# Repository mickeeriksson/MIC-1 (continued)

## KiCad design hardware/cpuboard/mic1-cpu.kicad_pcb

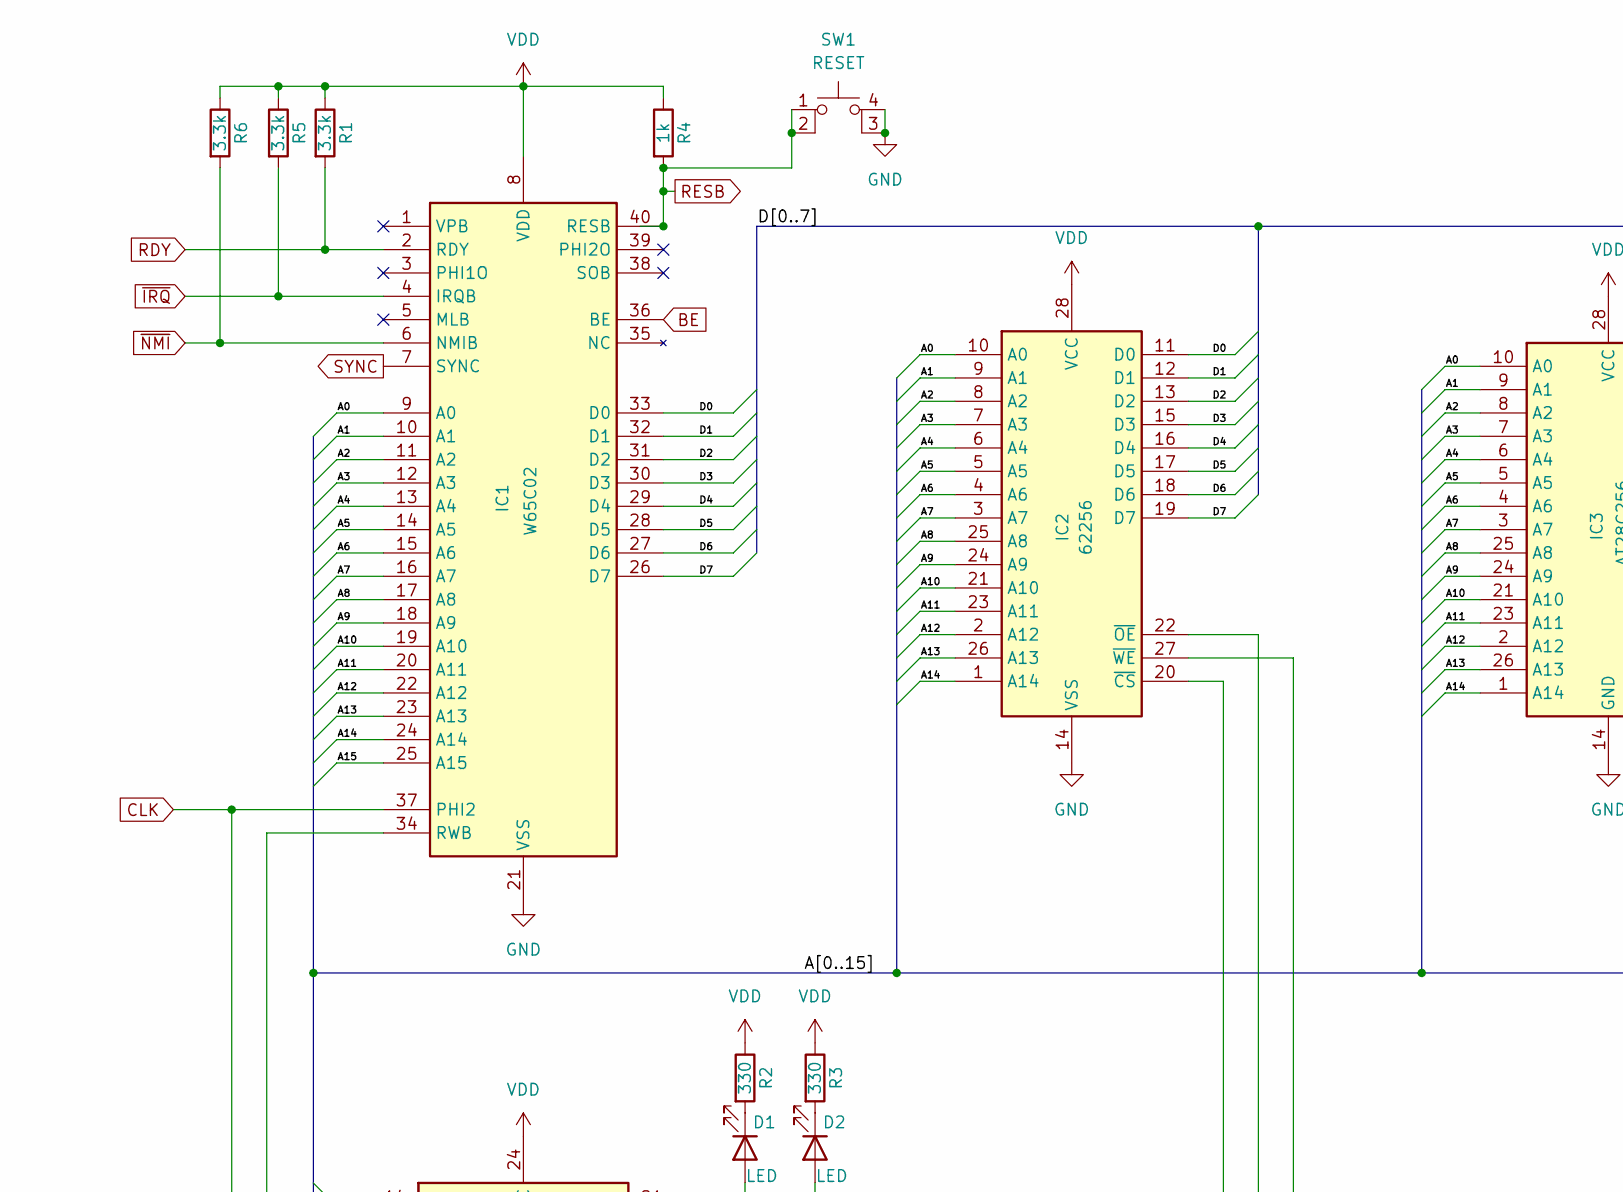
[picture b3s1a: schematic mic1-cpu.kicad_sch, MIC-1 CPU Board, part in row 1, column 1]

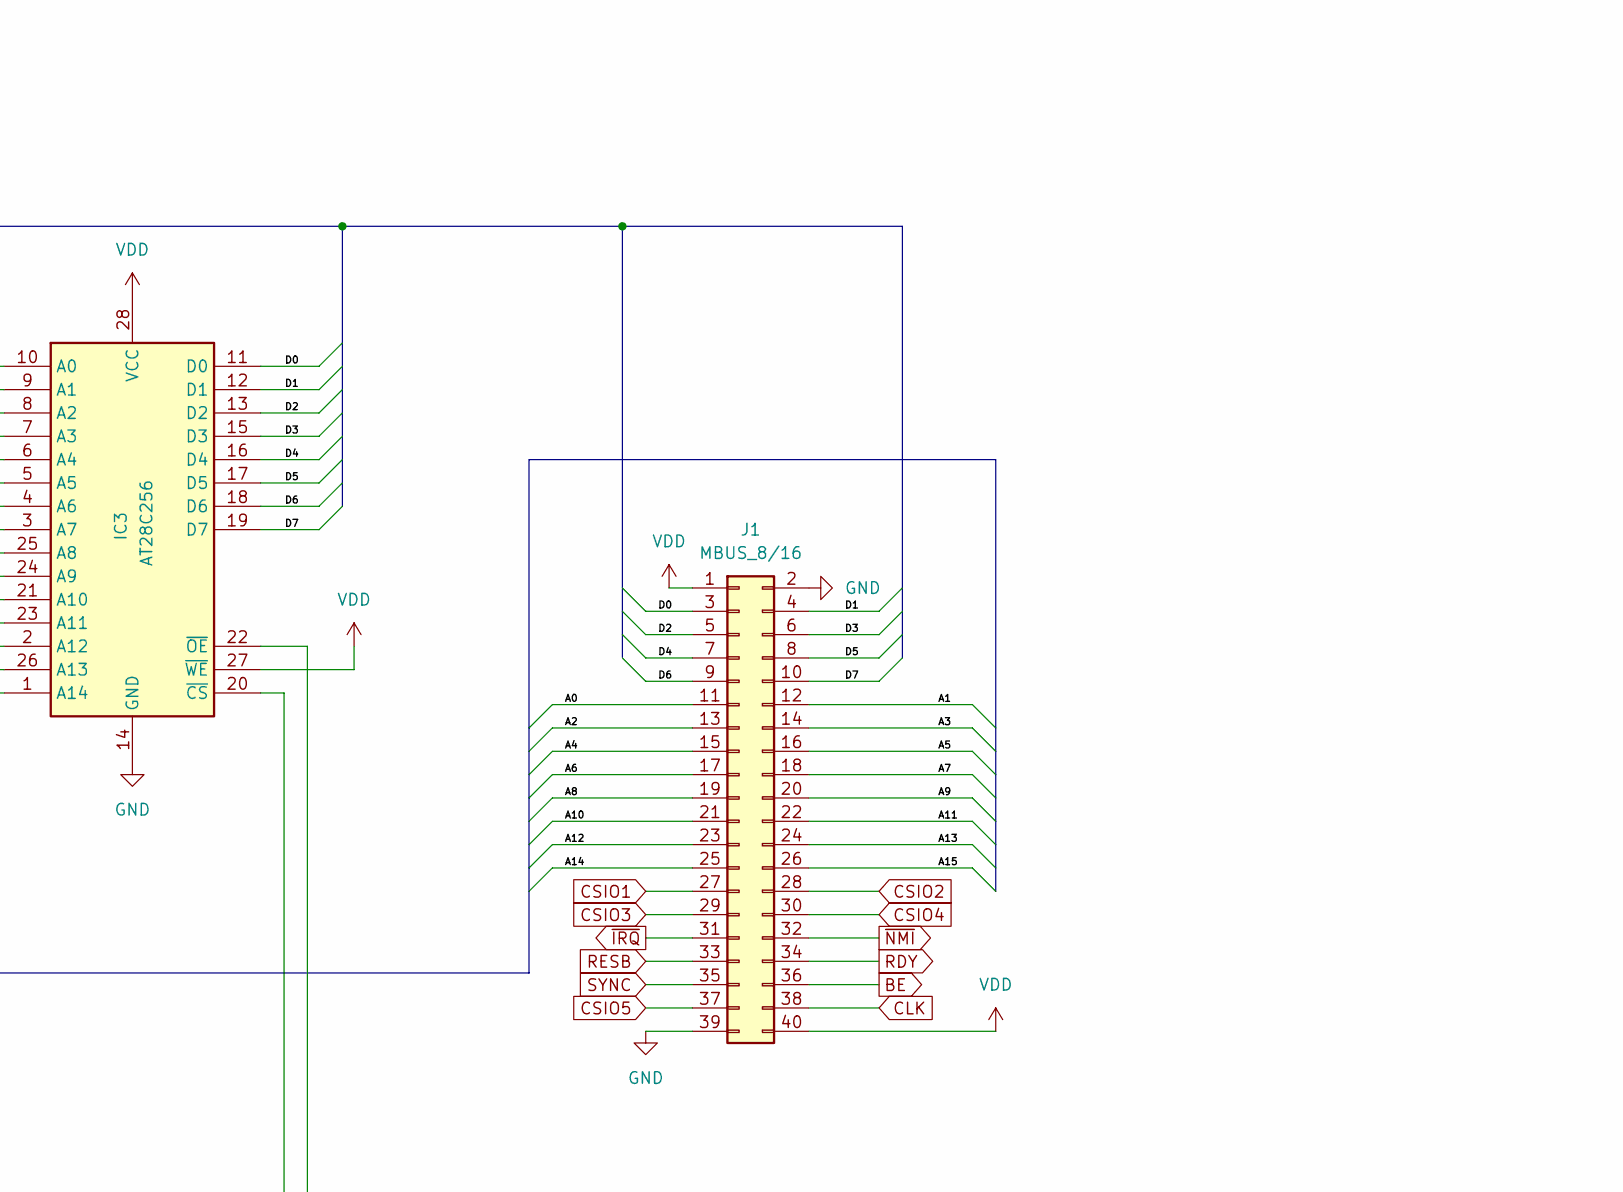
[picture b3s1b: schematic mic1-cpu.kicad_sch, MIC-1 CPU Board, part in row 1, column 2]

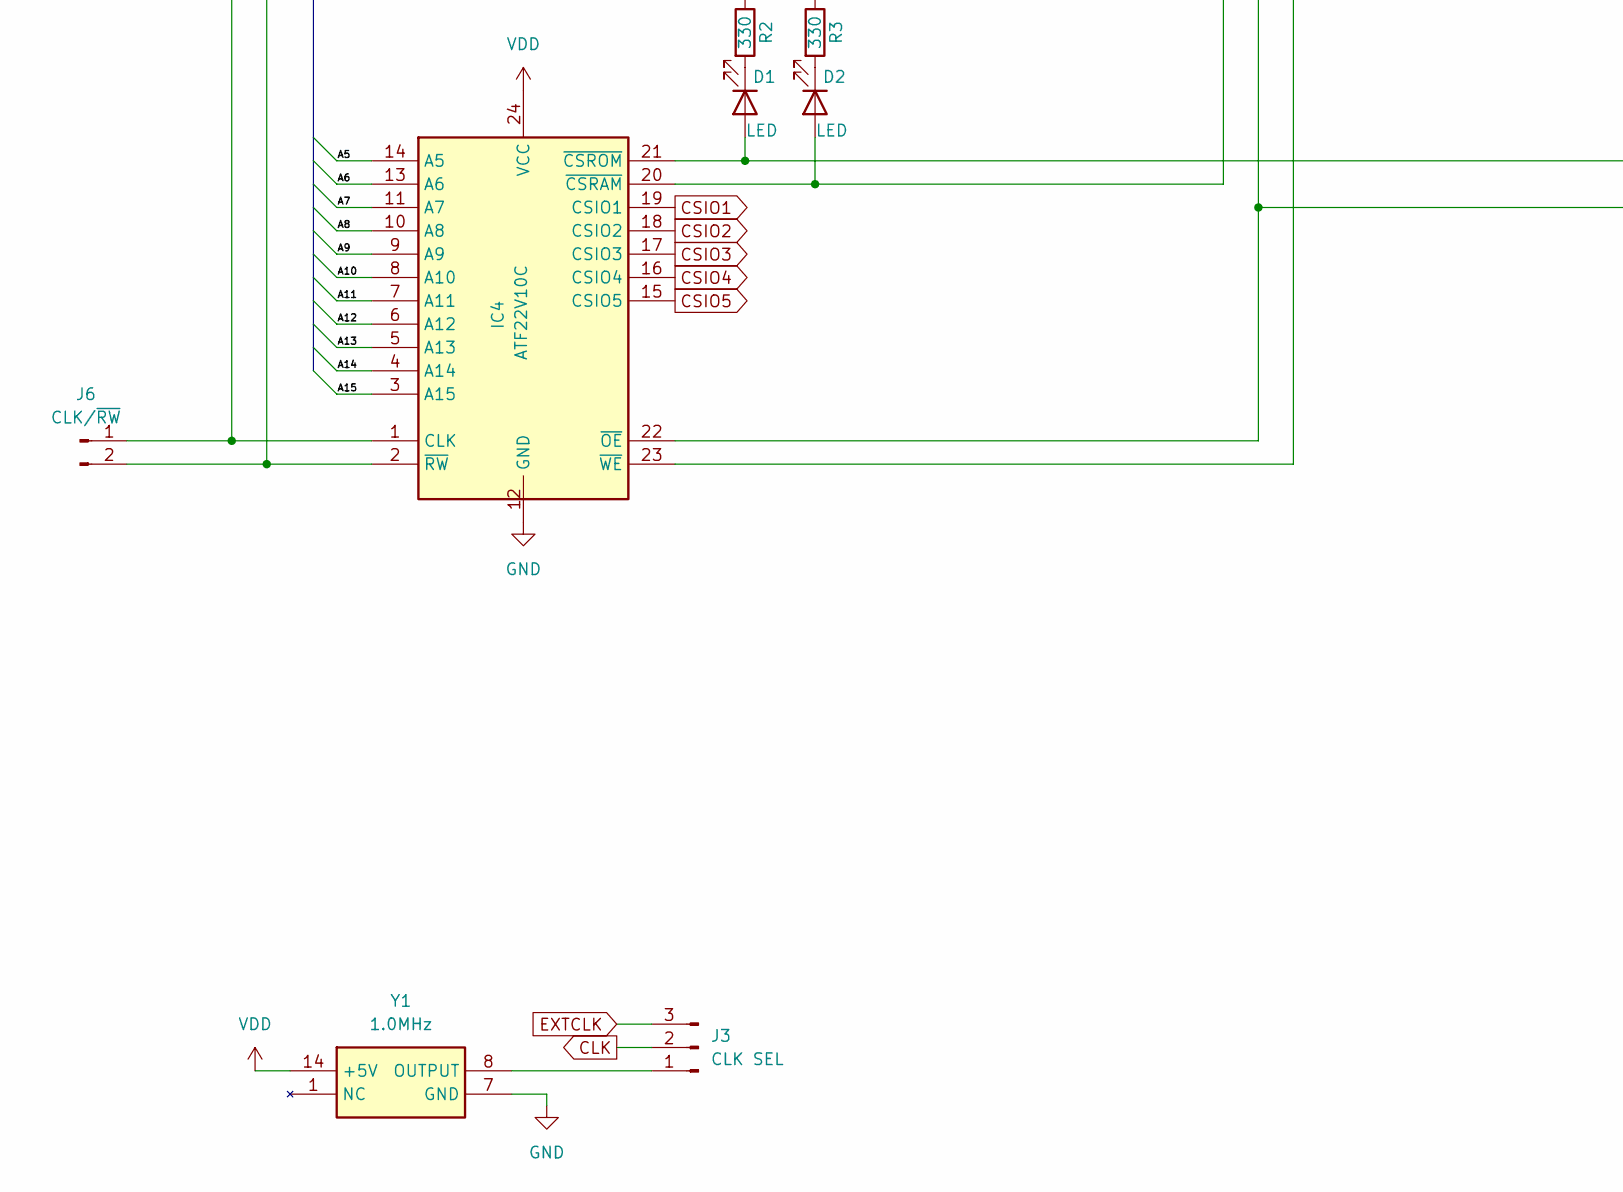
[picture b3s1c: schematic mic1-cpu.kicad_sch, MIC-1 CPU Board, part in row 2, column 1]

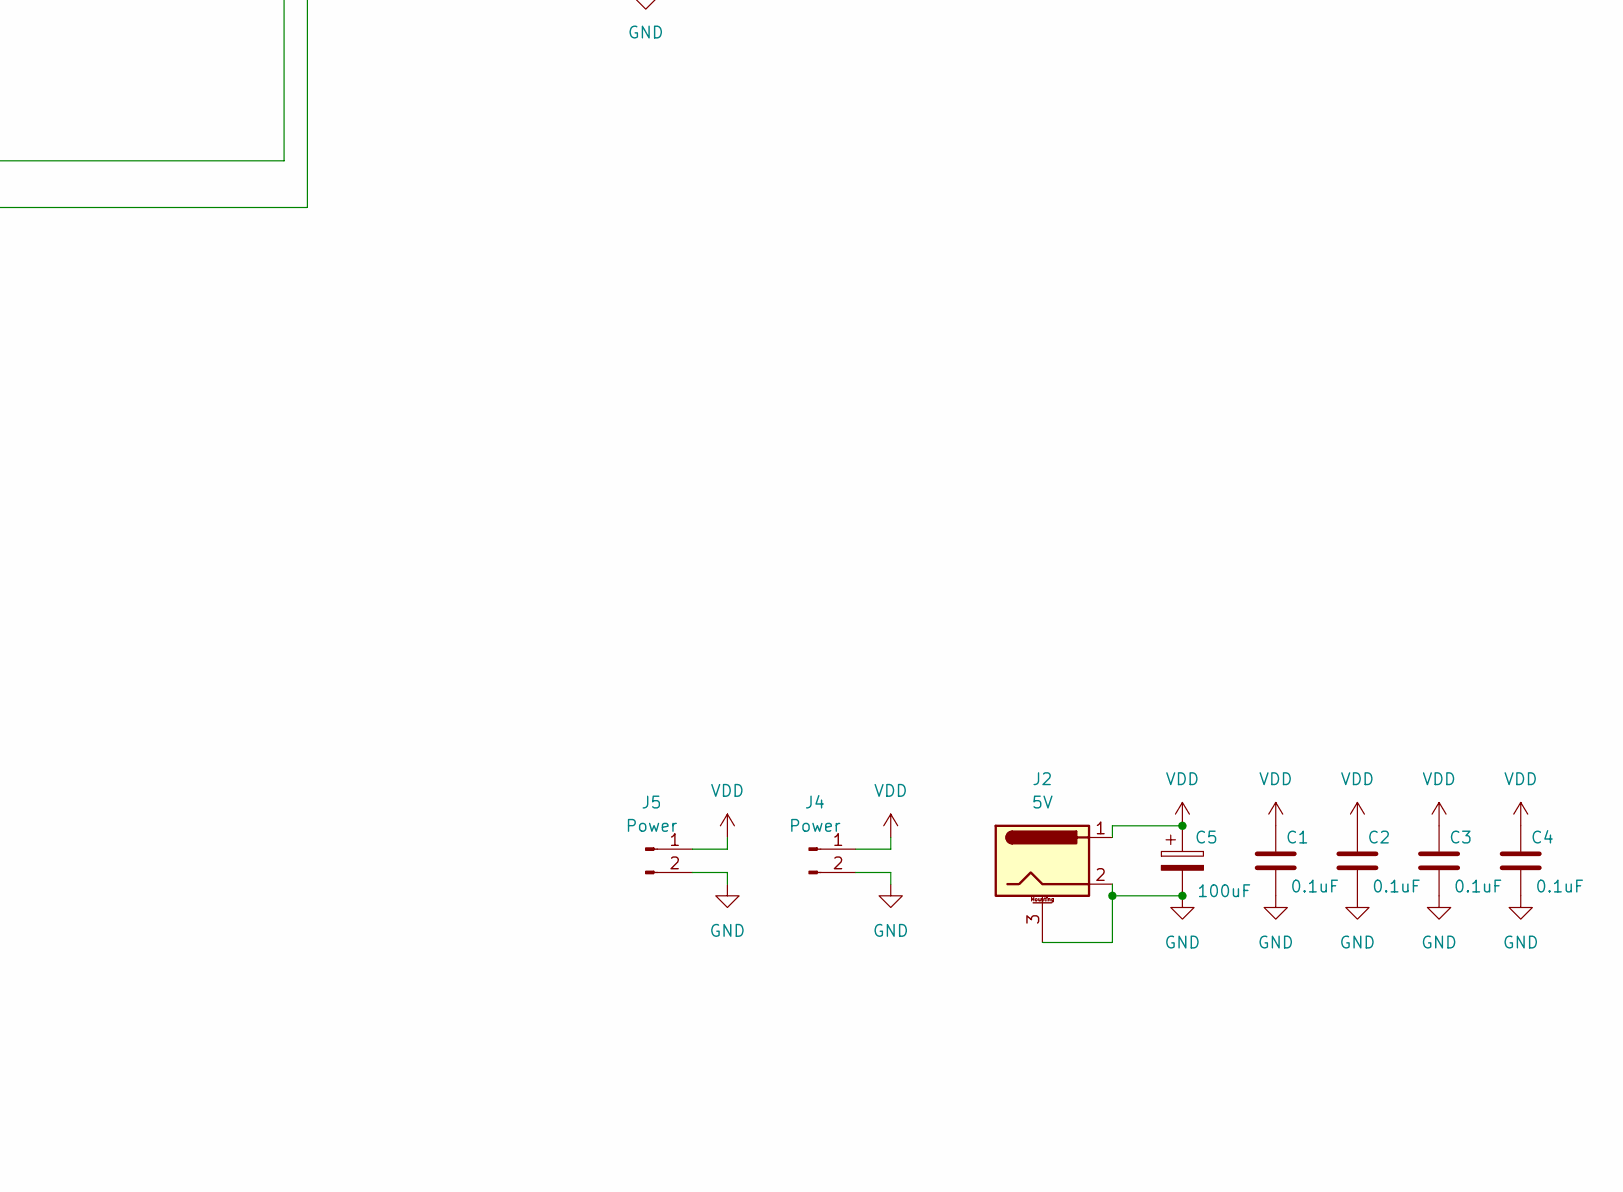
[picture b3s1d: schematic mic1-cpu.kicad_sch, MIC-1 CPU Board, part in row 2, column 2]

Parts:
C1, C2, C3, C4: 0.1uF; C_Disc_D3.0mm_W2.0mm_P2.50mm
C5: 100uF; CP_Radial_D5.0mm_P2.50mm
D1, D2: LED; LED_D5.0mm
IC1: W65C02; DIP-40_W15.24mm_Socket_LongPads; Mouser Part Number 955-W65C02S6TPG-14
IC2: 62256; DIP-28_W15.24mm_LongPads; Mouser Part Number 913-AS6C62256-55PCN
IC3: AT28C256; DIP_Socket-28_W11.9_W12.7_W15.24_W17.78_W18.5_3M_228-1277-0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; Mouser Part Number 556-AT28C25615PU
IC4: ATF22V10C; DIP-24_W7.62mm_Socket_LongPads; Mouser Part Number 556-AF22V10C15PU
J1: MBUS_8/16; PinHeader_2x20_P2.54mm_Vertical
J2: 5V; BarrelJack_GCT_DCJ200-10-A_Horizontal
J3: CLK SEL; PinHeader_1x03_P2.54mm_Vertical
J4, J5: Power; PinHeader_1x02_P2.54mm_Vertical
J6: CLK/~{RW}; PinHeader_1x02_P2.54mm_Vertical
R1, R5, R6: 3.3k; R_Axial_DIN0207_L6.3mm_D2.5mm_P7.62mm_Horizontal
R2, R3: 330; R_Axial_DIN0207_L6.3mm_D2.5mm_P7.62mm_Horizontal
R4: 1k; R_Axial_DIN0207_L6.3mm_D2.5mm_P7.62mm_Horizontal
SW1: RESET; SW_PUSH_6mm_H4.3mm
Y1: 1.0MHz; ECS100AX010; Mouser Part Number 520-TCF100-X

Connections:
/A0: IC1.9 (A0), IC2.10 (A0), IC3.10 (A0), J1.11
/A1: IC1.10 (A1), IC2.9 (A1), IC3.9 (A1), J1.12
/A2: IC1.11 (A2), IC2.8 (A2), IC3.8 (A2), J1.13
/A3: IC1.12 (A3), IC2.7 (A3), IC3.7 (A3), J1.14
/A4: IC1.13 (A4), IC2.6 (A4), IC3.6 (A4), J1.15
/A5: IC1.14 (A5), IC2.5 (A5), IC3.5 (A5), IC4.14 (A5), J1.16
/A6: IC1.15 (A6), IC2.4 (A6), IC3.4 (A6), IC4.13 (A6), J1.17
/A7: IC1.16 (A7), IC2.3 (A7), IC3.3 (A7), IC4.11 (A7), J1.18
/A8: IC1.17 (A8), IC2.25 (A8), IC3.25 (A8), IC4.10 (A8), J1.19
/A9: IC1.18 (A9), IC2.24 (A9), IC3.24 (A9), IC4.9 (A9), J1.20
/A10: IC1.19 (A10), IC2.21 (A10), IC3.21 (A10), IC4.8 (A10), J1.21
/A11: IC1.20 (A11), IC2.23 (A11), IC3.23 (A11), IC4.7 (A11), J1.22
/A12: IC1.22 (A12), IC2.2 (A12), IC3.2 (A12), IC4.6 (A12), J1.23
/A13: IC1.23 (A13), IC2.26 (A13), IC3.26 (A13), IC4.5 (A13), J1.24
/A14: IC1.24 (A14), IC2.1 (A14), IC3.1 (A14), IC4.4 (A14), J1.25
/A15: IC1.25 (A15), IC4.3 (A15), J1.26
/D0: IC1.33 (D0), IC2.11 (D0), IC3.11 (D0), J1.3
/D1: IC1.32 (D1), IC2.12 (D1), IC3.12 (D1), J1.4
/D2: IC1.31 (D2), IC2.13 (D2), IC3.13 (D2), J1.5
/D3: IC1.30 (D3), IC2.15 (D3), IC3.15 (D3), J1.6
/D4: IC1.29 (D4), IC2.16 (D4), IC3.16 (D4), J1.7
/D5: IC1.28 (D5), IC2.17 (D5), IC3.17 (D5), J1.8
/D6: IC1.27 (D6), IC2.18 (D6), IC3.18 (D6), J1.9
/D7: IC1.26 (D7), IC2.19 (D7), IC3.19 (D7), J1.10
BE: IC1.36 (BE), J1.36
CLK: IC1.37 (PHI2), IC4.1 (CLK), J1.38, J3.2, J6.1
CSIO1: IC4.19 (CSIO1), J1.27
CSIO2: IC4.18 (CSIO2), J1.28
CSIO3: IC4.17 (CSIO3), J1.29
CSIO4: IC4.16 (CSIO4), J1.30
CSIO5: IC4.15 (CSIO5), J1.37
EXTCLK: J3.3
GND: C1.2, C2.2, C3.2, C4.2, C5.2, IC1.21 (VSS), IC2.14 (VSS), IC3.14 (GND), IC4.12 (GND), J1.2, J1.39, J2.2, J2.3 (M), J4.2, J5.2, SW1.3 (K), SW1.4 (A), Y1.7 (GND)
unnamed: D1.2 (A), IC3.20 (~CS), IC4.21 (~CSROM)
unnamed: D1.1 (K), R2.2
unnamed: D2.2 (A), IC2.20 (~CS), IC4.20 (~CSRAM)
unnamed: D2.1 (K), R3.2
unnamed: IC1.34 (RWB), IC4.2 (~RW), J6.2
unnamed: IC2.22 (~OE), IC3.22 (~OE), IC4.22 (~OE)
unnamed: IC2.27 (~WE), IC4.23 (~WE)
unnamed: J3.1, Y1.8 (OUTPUT)
RDY: IC1.2 (RDY), J1.34, R1.2
RESB: IC1.40 (RESB), J1.33, R4.2, SW1.1, SW1.2
SYNC: IC1.7 (SYNC), J1.35
VDD: C1.1, C2.1, C3.1, C4.1, C5.1, IC1.8 (VDD), IC2.28 (VCC), IC3.27 (~WE), IC3.28 (VCC), IC4.24 (VCC), J1.1, J1.40, J2.1, J4.1, J5.1, R1.1, R2.1, R3.1, R4.1, R5.1, R6.1, Y1.14 (+5V)
~IRQ: IC1.4 (IRQB), J1.31, R5.2
~NMI: IC1.6 (NMIB), J1.32, R6.2

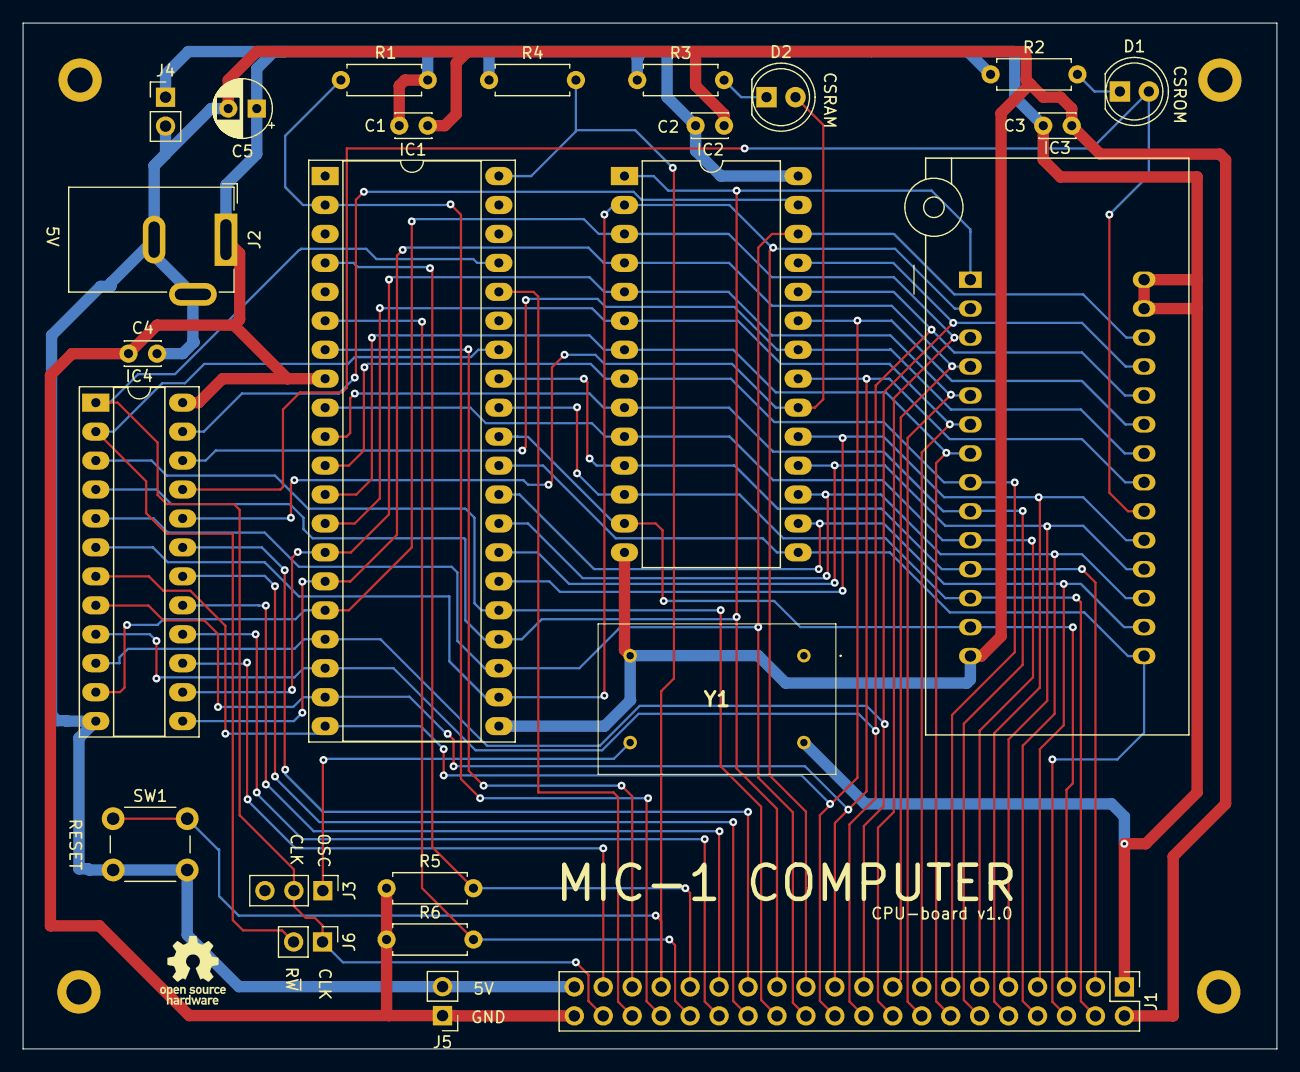
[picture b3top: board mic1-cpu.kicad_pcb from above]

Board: 2 copper layers, 110.0 x 90.0 mm, 29 parts (0 on the bottom side), 46 nets.

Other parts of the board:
Hole1, Hole2: MountingHole_2.2mm_M2_DIN965_Pad
Hole3, Hole4: (no value)

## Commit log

2024-11-19 "Hello World" on Symon
2024-12-01 with address encoder
2024-12-09 KiCAD CPU Board
2024-12-15 KiCAD BusBoard + DebugBoard
2025-08-03 reuse CSIO5 to get RWB on bus instead
